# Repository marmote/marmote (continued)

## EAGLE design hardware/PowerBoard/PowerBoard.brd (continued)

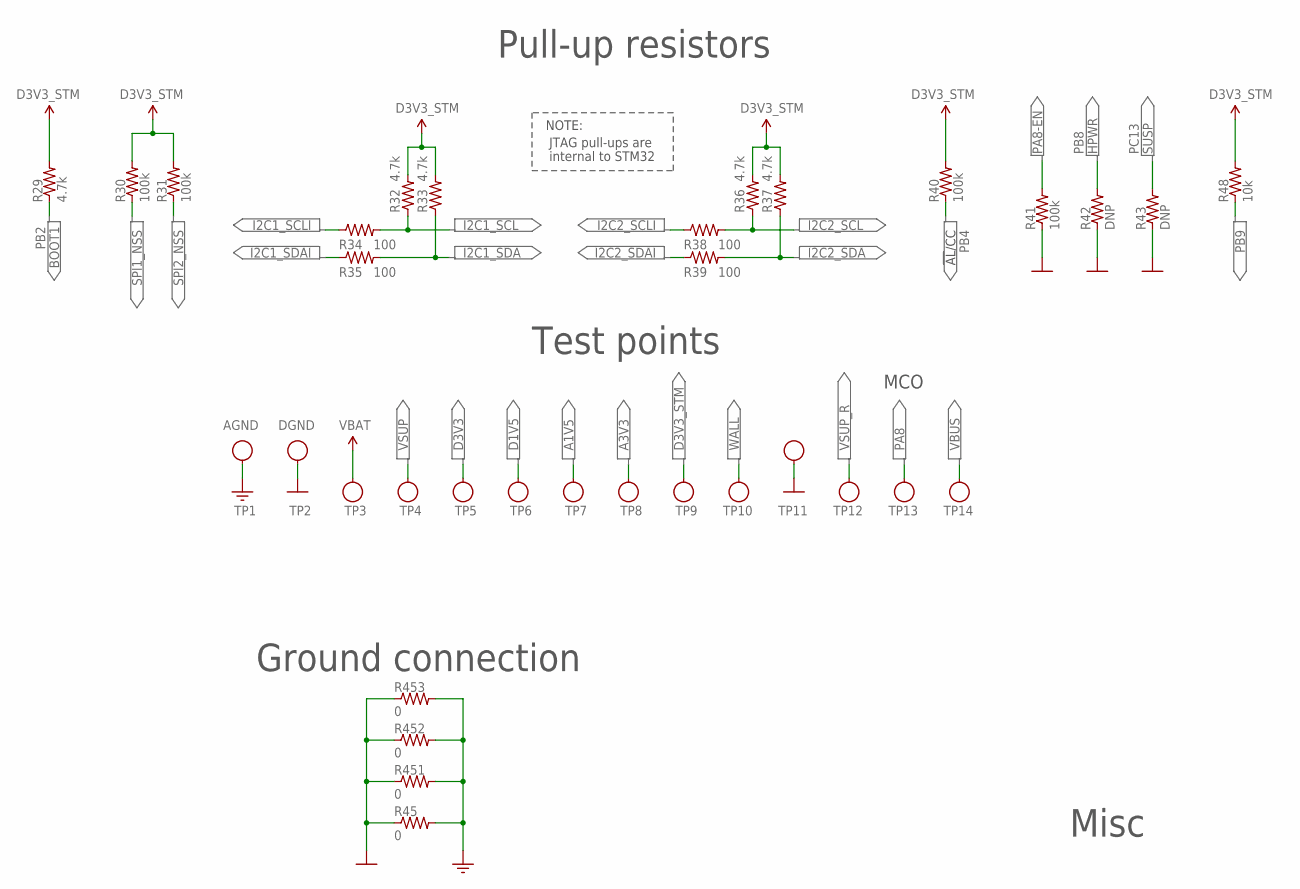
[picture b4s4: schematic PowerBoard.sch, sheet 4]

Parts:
R29, R32, R33, R36, R37: 4.7k; R0603
R30, R31, R40, R41: 100k; R0603
R34, R35, R38, R39: 100; R0603
R42, R43: DNP; R0603
R45, R451, R452, R453: 0; R0603
R48: 10k; R0603
TP1, TP2, TP3, TP4, TP5, TP6, TP7, TP8, TP9, TP10, TP11, TP12, TP13: TESTPOINT
TP14: TESTPOINT; MPN 5122; DIGI-KEY# 5122K-ND

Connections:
A1V5: TP7.1; also elsewhere on the board
A3V3: TP8.1; also elsewhere on the board
AGND: R45.2, R451.2, R452.2, R453.2, TP1.1; also elsewhere on the board
D1V5: TP6.1; also elsewhere on the board
D3V3: TP5.1; also elsewhere on the board
D3V3_STM: R29.2, R30.2, R31.2, R32.2, R33.2, R36.2, R37.2, R40.2, R48.2, TP9.1; also elsewhere on the board
DGND: R41.1, R42.1, R43.1, R45.1, R451.1, R452.1, R453.1, TP2.1, TP11.1; also elsewhere on the board
I2C1_SCL: R32.1, R34.2; also elsewhere on the board
I2C1_SCLI: R34.1; also elsewhere on the board
I2C1_SDA: R33.1, R35.2; also elsewhere on the board
I2C1_SDAI: R35.1; also elsewhere on the board
I2C2_SCL: R36.1, R38.2; also elsewhere on the board
I2C2_SCLI: R38.1; also elsewhere on the board
I2C2_SDA: R37.1, R39.2; also elsewhere on the board
I2C2_SDAI: R39.1; also elsewhere on the board
PA8: TP13.1; also elsewhere on the board
PA8-EN: R41.2; also elsewhere on the board
PB2: R29.1; also elsewhere on the board
PB4: R40.1; also elsewhere on the board
PB8: R42.2; also elsewhere on the board
PB9: R48.1; also elsewhere on the board
PC13: R43.2; also elsewhere on the board
SPI1_NSS: R30.1; also elsewhere on the board
SPI2_NSS: R31.1; also elsewhere on the board
VBAT: TP3.1; also elsewhere on the board
VBUS: TP14.1; also elsewhere on the board
VSUP: TP4.1; also elsewhere on the board
VSUP_R: TP12.1; also elsewhere on the board
WALL: TP10.1; also elsewhere on the board

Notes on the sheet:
Test points
Pull-up resistors
!AL!/CC
BOOT1
MCO
JTAG pull-ups are
internal to STM32
NOTE:
SUSP
HPWR
Ground connection

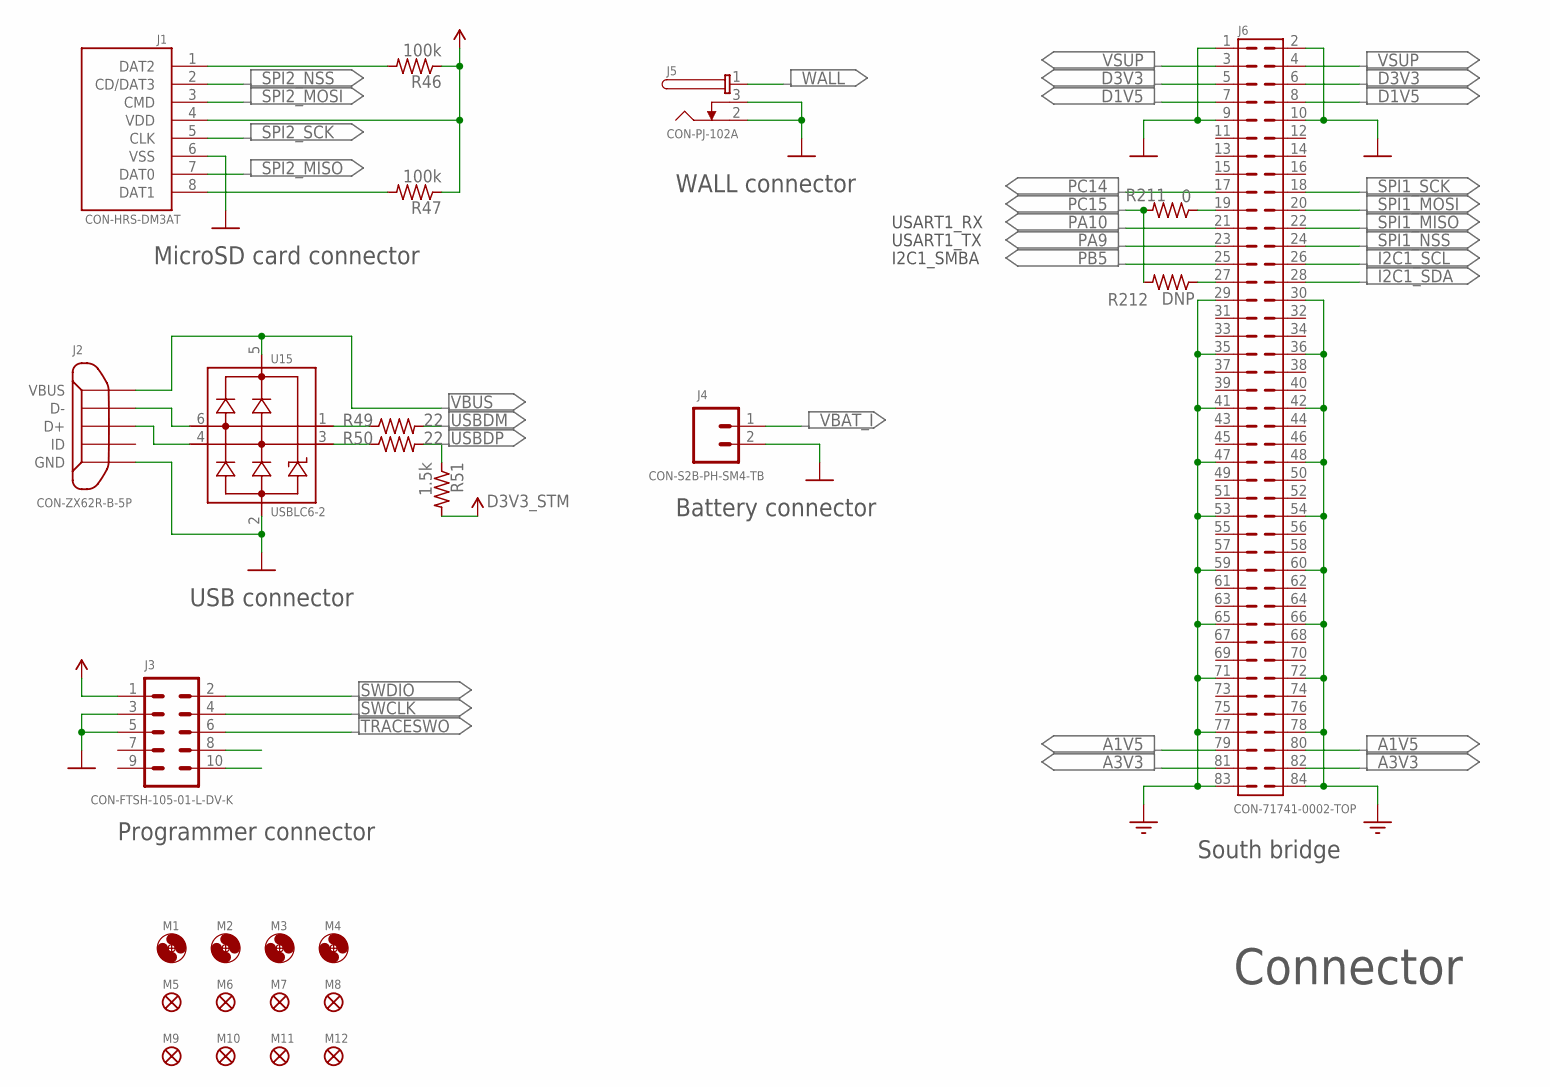
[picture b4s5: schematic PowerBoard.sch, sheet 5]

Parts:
J1: CON-HRS-DM3AT; HRS-DM3AT
J2: CON-ZX62R-B-5P; ZX62R-B-5P
J3: CON-FTSH-105-01-L-DV-K; FTSH-105-01-L-DV-K
J4: CON-S2B-PH-SM4-TB; S2B-PH-SM4-TB
J5: CON-PJ-102A; PJ-102A
J6: CON-71741-0002-TOP; 71741-0002
M1, M2, M3, M4: MOUNT-HOLE3.3; 3,3
M5, M6, M7, M8, M9, M10, M11, M12: FIDUCIAL1X2; FIDUCIAL-1X2
R46, R47: 100k; R0603
R49, R50: 22; R0603
R51: 1.5k; R0603
R211: 0; R0603
R212: DNP; R0603
U15: USBLC6-2; SOT23-6L

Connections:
A1V5: J6.79, J6.80; also elsewhere on the board
A3V3: J6.81, J6.82; also elsewhere on the board
AGND: J6.29, J6.30, J6.35, J6.36, J6.41, J6.42, J6.47, J6.48, J6.53, J6.54, J6.59, J6.60, J6.65, J6.66, J6.71, J6.72, J6.77, J6.78, J6.83, J6.84; also elsewhere on the board
D1V5: J6.7, J6.8; also elsewhere on the board
D3V3: J6.5, J6.6; also elsewhere on the board
D3V3_STM: J1.4 (VDD), J3.1, R46.1, R47.1, R51.2; also elsewhere on the board
DGND: J1.6 (VSS), J2.5 (GND), J3.3, J3.5, J4.2, J5.2, J5.3, J6.1, J6.2, J6.9, J6.10, U15.2 (GND); also elsewhere on the board
I2C1_SCL: J6.26; also elsewhere on the board
I2C1_SDA: J6.28; also elsewhere on the board
JNTRST: J3.10
JTDI: J3.8
unnamed: R50.1, U15.3 (IO2)
unnamed: R49.1, U15.1 (IO1)
unnamed: J6.27, R212.1
unnamed: J6.19, R211.1
unnamed: J1.1 (DAT2), R46.2
unnamed: J1.8 (DAT1), R47.2
PA9: J6.23; also elsewhere on the board
PA10: J6.21; also elsewhere on the board
PB5: J6.25; also elsewhere on the board
PC14: J6.17; also elsewhere on the board
PC15: R211.2, R212.2; also elsewhere on the board
SPI1_MISO: J6.22; also elsewhere on the board
SPI1_MOSI: J6.20; also elsewhere on the board
SPI1_NSS: J6.24; also elsewhere on the board
SPI1_SCK: J6.18; also elsewhere on the board
SPI2_MISO: J1.7 (DAT0); also elsewhere on the board
SPI2_MOSI: J1.3 (CMD); also elsewhere on the board
SPI2_NSS: J1.2 (CD/DAT3); also elsewhere on the board
SPI2_SCK: J1.5 (CLK); also elsewhere on the board
SWCLK: J3.4; also elsewhere on the board
SWDIO: J3.2; also elsewhere on the board
TRACESWO: J3.6; also elsewhere on the board
USBD+: J2.3 (D+), U15.4 (IO2)
USBD-: J2.2 (D-), U15.6 (IO1)
USBDM: R49.2; also elsewhere on the board
USBDP: R50.2, R51.1; also elsewhere on the board
VBAT_I: J4.1; also elsewhere on the board
VBUS: J2.1 (VBUS), U15.5 (VBUS); also elsewhere on the board
VSUP: J6.3, J6.4; also elsewhere on the board
WALL: J5.1; also elsewhere on the board

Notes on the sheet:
MicroSD card connector
South bridge
Programmer connector
USB connector
WALL connector
Battery connector
USART1_TX
USART1_RX
I2C1_SMBA

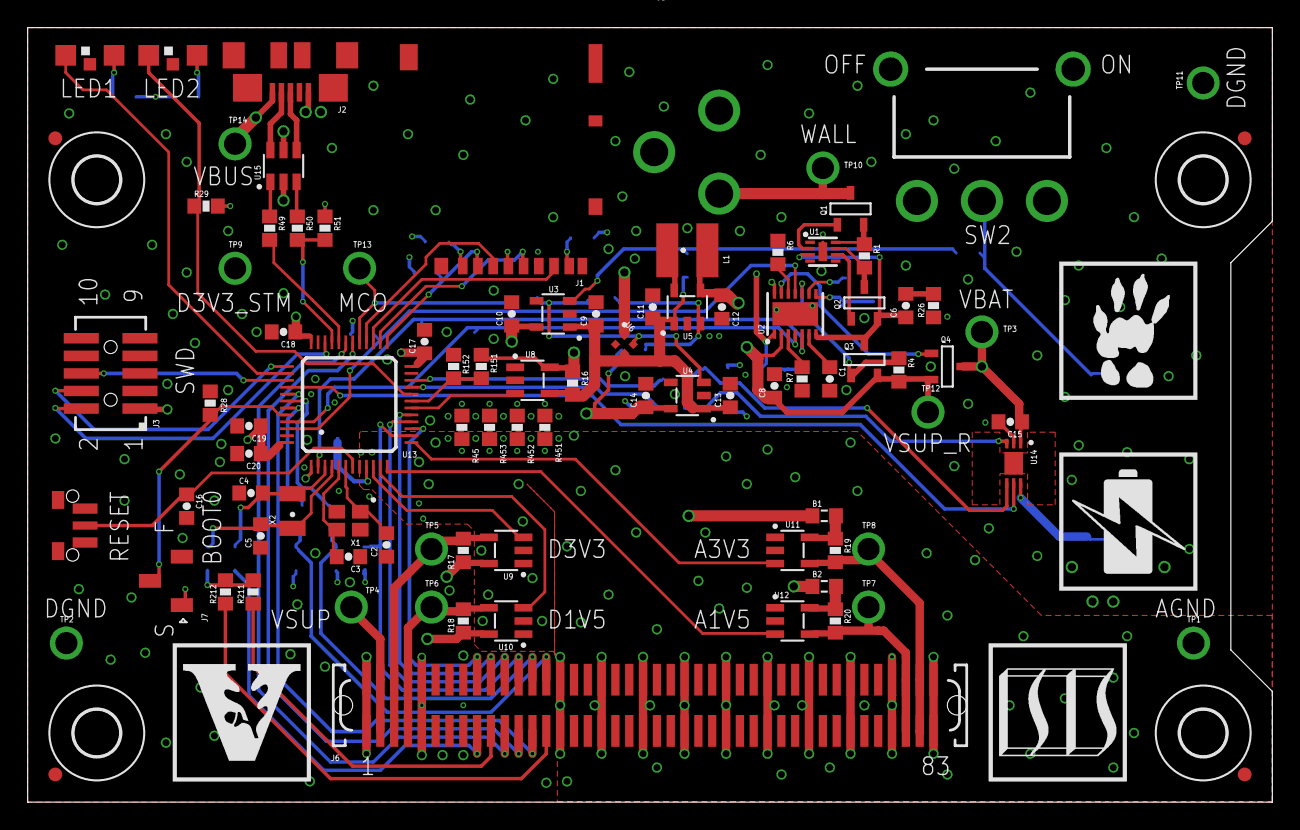
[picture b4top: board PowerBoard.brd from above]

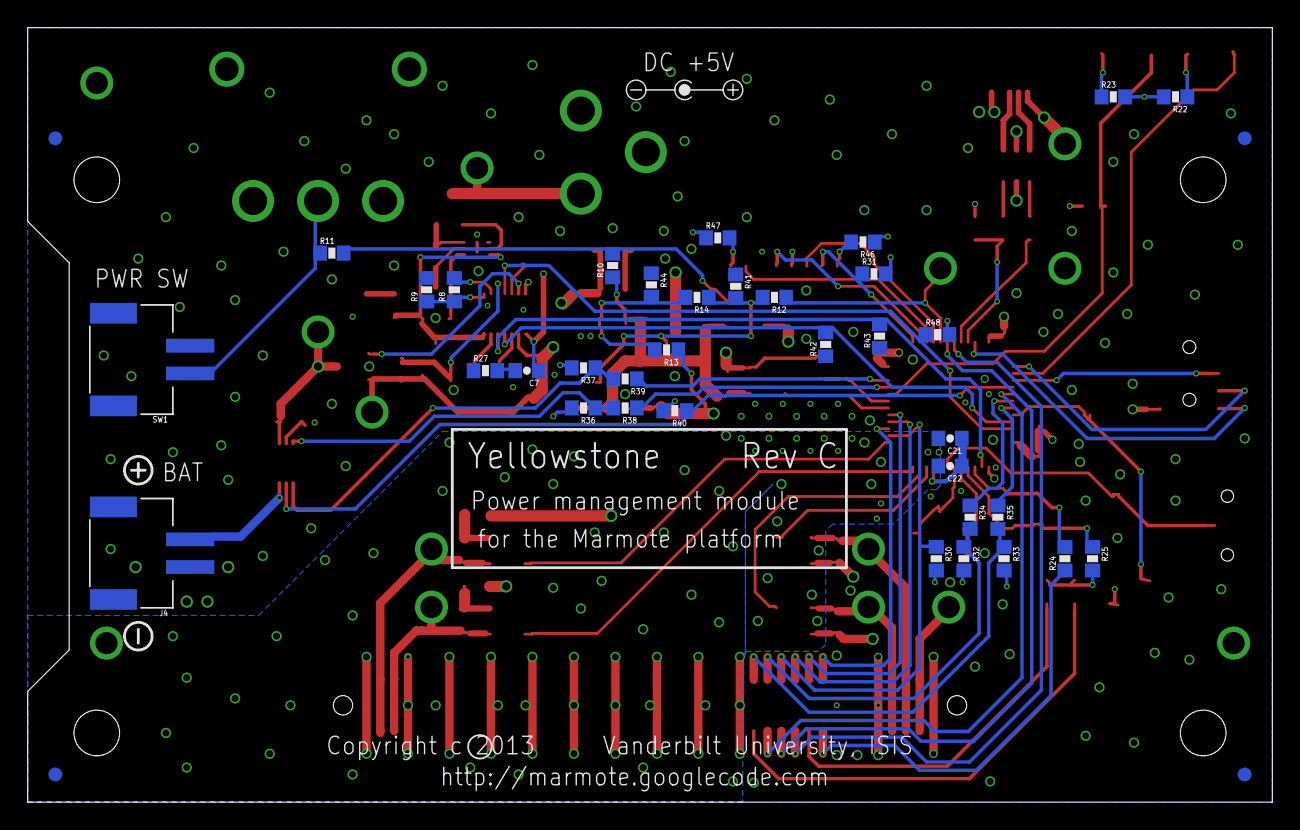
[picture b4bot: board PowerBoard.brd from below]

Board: 4 copper layers, 90.0 x 56.0 mm, 140 parts (39 on the bottom side), 92 nets.

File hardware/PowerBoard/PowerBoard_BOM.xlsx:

Bill of Materials for 'Marmote - Power Supply Board (Rev B)'
Item # | Reference | Value | Package | Manufacturer | Manufacturer Part # | Supplier | Supplier Part # | Details | Qty | Unit Price | Total Cost
1 | B1, B2 | 20mOhm@DC, 70Ohm@100MHz | BEAD0603 | Murata | BLM18SG700TN1D | Digi-Key | 490-5224-1-ND | FERRITE CHIP 70OHM 4A 0603 | 2 | 0.35299999999999998 | 0.70599999999999996
2 | C4, C5 | DNP | C0603 | TDK | C1608C0G1H040B | Digi-Key | 445-5028-1-ND | CAP CER 4.0PF 50V C0G 0603 | 2 | 0.16 | 0.32
3 | C2, C3 | 10pF | C0603 | TDK | C1608C0G1H100J | Digi-Key | 445-6852-1-ND | CAP CER 10PF 50V C0G 5% 0603 | 2 | 0.12 | 0.24
4 | C22 | 10nF | C0603 | TDK | C1608X7R1E103K | Digi-Key | 445-5100-1-ND | CAP CER 10000PF 25V X7R 10% 0603 | 1 | 0.08 | 0.08
5 | C15, C16, C17, C18, C19 | 0.1uF | C0603 | TDK | C1608X7R1C104K | Digi-Key | 445-1317-1-ND | CAP CER .10UF 16V 10% X7R 0603 | 5 | 0.08 | 0.4
6 | C1 | 0.15uF | C0603 | TDK | C1608X7R1C154K | Digi-Key | 445-5123-1-ND | CAP CER .15UF 16V 10% X7R 0603 | 1 | 0.2 | 0.2
7 | C21 | 1uF | C0603 | TDK | C1608X7R1C105K | Digi-Key | 445-1604-1-ND | CAP CER 1.0UF 16V X7R 10% 0603 | 1 | 0.23 | 0.23
8 | C7, C8, C10, C11, C14, C20 | 4.7uF | C0603 | TDK | C1608X5R0J475K | Digi-Key | 445-5178-1-ND | CAP CER 4.7UF 6.3V X5R 0603 | 6 | 0.36 | 2.16
9 | C6, C9, C12, C13 | 10uF | C0603 | TDK | C1608X5R0J106M | Digi-Key | 445-4112-1-ND | CAP CER 10UF 6.3V X5R 20% 0603 | 4 | 0.46 | 1.84
10 | J1 | CON-HRS-DM3AT | CON-HRS-DM3AT | Hirose | DM3AT-SF-PEJM5 | Digi-Key | HR1964CT-ND | CONN MICRO SD R/A PUSH-PUSH SMD | 1 | 3.01 | 3.01
11 | J2 | CON-ZX62R-B-5P | CON-ZX62R-B-5P | Hirose | ZX62R-B-5P | Digi-Key | H11574CT-ND | CONN RCPT MICRO USB B SMD R/A | 1 | 1.56 | 1.56
12 | J3 | CON-FTSH-105-01-L-DV-K | CON-FTSH-105-01-L-DV-K | Samtec | FTSH-105-01-L-DV-K | Digi-Key | FTSH-105-01-L-DV-K-ND | CONN HEADER 10 POS DUAL .05" SMD | 1 | 3.36 | 3.36
13 | J4, SW1 | CON-S2B-PH-SM4-TB | CON-S2B-PH-SM4-TB | JST | S2B-PH-SM4-TB(LF)(SN) | Digi-Key | 455-1749-1-ND | CONN HEADER PH SIDE 2POS 2MM SMD | 2 | 0.5 | 1
14 | J5 | CON-PJ-102A | CON-PJ-102A | CUI | PJ-102A | Digi-Key | CP-102A-ND | CONN JACK POWER 2.1MM PCB | 1 | 0.8 | 0.8
15 | J6 | CON-71741-0002 | CON-71741-0002 | Molex | 71741-0002 | Digi-Key | WM3498CT-ND | MEZZANINE 1MM BTB PLUG 84CKT | 1 | 6.24 | 6.24
16 | J7 | SWITCH-CJS-1200-1200 | J-Lead | CJS | CJS-1200TA | Digi-Key | 563-1021-1-ND | CJS-1200 SPDT Switch | 1 | 0.97 | 0.97
17 | L1 | 1.6uH | L-VLCF4018T | TDK | VLCF4018T-1R6N1R7-2 | Digi-Key | 445-3171-1-ND | INDUCTOR POWER 1.6UH 1.7A SMD | 1 | 0.72 | 0.72
18 | LED2 | ORANGE | LED1208-RA | Kingbright | APECVA3010SECK | Digi-Key | 754-1367-1-ND | LED 3X1MM 601NM ORN RA CHIP SMD | 1 | 0.28000000000000003 | 0.28000000000000003
19 | LED1 | GREEN | LED1208-RA | Kingbright | APECVA3010MGC | Digi-Key | 754-1364-1-ND | LED 3.0X1.0MM 568NM GRN RA SMD | 1 | 0.63 | 0.63
20 | Q1 | SI2323CDS | SI2323CDS | Vishay | SI2323CDS-T1-GE3 | Digi-Key | SI2323CDS-T1-GE3CT-ND | MOSFET P-CH 20V SOT-23 | 1 | 0.76 | 0.76
21 | Q2 | SI2312CDS | SI2312CDS | Vishay | SI2312CDS-T1-GE3 | Digi-Key | SI2312CDS-T1-GE3CT-ND | MOSFET N-CH 20V SOT-23 | 1 | 0.45 | 0.45
22 | Q3, Q4 | SI2333CDS | SI2333CDS | Vishay | SI2333CDS-T1-GE3 | Digi-Key | SI2333CDS-T1-GE3CT-ND | MOSFET P-CH D-S 12V SOT-23 | 2 | 0.84 | 1.68
23 | R13, R42, R43, R44, R212 | DNP | R0603 |  |  |  |  |  | 5 |  | 0
24 | R1, R12, R14, R211, R24, R25, R45, R451, R452, R453 | 0 | R0603 | Rohm | MCR03ERTJ000 | Digi-Key | RHM0.0GCT-ND | RES 0.0 OHM 1/10W 0603 SMD | 10 | 1.7999999999999999E-2 | 0.18
25 | R16, R17, R18, R19, R20 | 50m | R0603 | Vishay | WSL0603R0500FEA18 | Digi-Key | WSLL-.05CT-ND | RES .05 OHM 0.2W 1% 0603 SMD | 5 | 1.32 | 6.6000000000000005
26 | R26, R27 | 1 | R0603 | Rohm | MCR03EZPJ1R0 | Digi-Key | RHM1.0GCT-ND | RES 1.0 OHM 1/10W 5% 0603 SMD | 2 | 1.7999999999999999E-2 | 3.5999999999999997E-2
27 | R49, R50 | 22 | R0603 | Rohm | MCR03EZPFX22R0 | Digi-Key | RHM22.0HCT-ND | RES 22.0 OHM 1/10W 1% 0603 SMD | 2 | 2.3E-2 | 4.5999999999999999E-2
28 | R22, R34, R35, R38, R39 | 100 | R0603 | Rohm | MCR03ERTJ101 | Digi-Key | RHM100GCT-ND | RES 100 OHM 1/10W 5% 0603 SMD | 5 | 1.7999999999999999E-2 | 0.09
29 | R23 | 330 | R0603 | Rohm | MCR03EZPFX3300 | Digi-Key | RHM330HCT-ND | RES 330 OHM 1/10W 1% 0603 SMD | 1 | 2.3E-2 | 2.3E-2
30 | R51 | 1.5k | R0603 | Rohm | MCR03ERTF1501 | Digi-Key | RHM1.50KCFCT-ND | RES 1.50K OHM 1/10W 1% 0603 SMD | 1 | 0.21 | 0.21
31 | R7 | 2.1k | R0603 | Rohm | MCR03EZPFX2101 | Digi-Key | RHM2.10KHCT-ND | RES 2.10K OHM 1/10W 1% 0603 SMD | 1 | 2.3E-2 | 2.3E-2
32 | R11, R29, R32, R33, R36, R37 | 4.7k | R0603 | Rohm | MCR03ERTJ472 | Digi-Key | RHM4.7KGCT-ND | RES 4.7K OHM 1/10W 5% 0603 SMD | 6 | 1.7999999999999999E-2 | 0.10799999999999998
33 | R9 | 10k | NTCG06 | Vishay/Dale | NTHS0603N02N1002JE | Digi-Key | 541-1107-1-ND | THERMISTOR NTC 10K OHM 5% 0603 | 1 | 1 | 1
34 | R4, R8, R48 | 10k | R0603 | Rohm | MCR03ERTF1002 | Digi-Key | RHM10.0KHCT-ND | RES 10.0K OHM 1/10W 1% 0603 SMD | 3 | 2.3E-2 | 6.9000000000000006E-2
35 | R6, R10, R28, R30, R31, R40, R41, R46, R47, R151, R152 | 100k | R0603 | Rohm | MCR03ERTF1003 | Digi-Key | RHM100KHCT-ND | RES 100K OHM 1/10W 1% 0603 SMD | 11 | 2.3E-2 | 0.253
36 | SW2 | SWITCH-MS12ASG30 | SWITCH-MS12ASG30 | NKK | MS12ASG30 | Digi-Key | 360-2390-ND | SW SLIDE SPDT 0.4VA GOLD R/A PC | 1 | 5.45 | 5.45
37 | SW3 | SWITCH-ESWITCH-TL3340G | SWITCH-ESWITCH-TL3340G | E-Switch | TL3340AF160QG | Digi-Key | EG4627CT-ND | SWITCH TACTILE SPST-NO 0.05A 12V | 1 | 0.29099999999999998 | 0.29099999999999998
38 | TP3, TP4, TP5, TP6, TP9, TP10, TP12, TP14 | TESTPOINT | TESTPOINT-BLUE | Keystone | 5122 | Digi-Key | 5122K-ND | TEST POINT PC COMPACT T/H BLUE | 7 | 0.38 | 2.66
39 | TP7, TP8 | TESTPOINT | TESTPOINT-GREEN | Keystone | 5121 | Digi-Key | 5121K-ND | TEST POINT PC COMPACT T/H GREEN | 2 | 0.38 | 0.76
40 | TP13 | TESTPOINT | TESTPOINT-RED | Keystone | 5005 | Digi-Key | 5005K-ND | TEST POINT PC COMPACT .063"D RED | 1 | 0.36 | 0.36
41 | TP1, TP2, TP11 | TESTPOINT | TESTPOINT-YELLOW | Keystone | 5009 | Digi-Key | 5009K-ND | TEST POINT PC COMPACT .063"D YLW | 3 | 0.36 | 1.08
42 | U1 | LTC4361-2DC | LTC4361-2DC | Linear Technology | LTC4361IDC-2#TRMPBF | Digi-Key | LTC4361IDC-2#TRMPBFCT-ND | IC OVERVOLTAGE PROT CONT 8-DFN | 1 | 3.78 | 3.78
43 | U13 | STM32F10XCXT6 | STM32F10XCXT6 | STMicroelectronics | STM32F102CBT6 | Digi-Key | 497-8308-ND | MCU ARM 32BIT 128KB FLASH 48LQFP | 1 | 8.9499999999999993 | 8.9499999999999993
44 | U14 | LTC2942-1 | LTC2942-1 | Linear Technology | LTC2942CDCB-1#TRMPBF | Digi-Key | LTC2942CDCB-1#TRMPBFCT-ND | IC FUEL/GAS GAUGE LI-ION 1A 6DFN | 1 | 4.51 | 4.51
45 | U15 | USBLC6-2 | USBLC6-2 | STMicroelectronics | USBLC6-2SC6 | Digi-Key | 497-5235-1-ND | IC ESD PROTECTION LO CAP SOT23-6 | 1 | 1 | 1
46 | U2 | LTC4085 | LTC4085 | Linear Technology | LTC4085EDE#PBF | Digi-Key | LTC4085EDE#PBF-ND | IC USB POWER MANAGER 14-DFN | 1 | 3.3 | 3.3
47 | U3, U4 | XC6220B331MR-G | XC6220B331MR-G | Torex | XC6220B331MR-G | Digi-Key | 893-1133-1-ND | IC REG LDO 3.3V 1A SOT-25 | 2 | 0.88 | 1.76
48 | U5 | XC9236A15DMR-G | XC9236A15DMR-G | Torex | XC9236A15DMR-G | Digi-Key | 893-1120-1-ND | IC BUCK SYNC 1.5V .6A SOT-25 3MHZ | 1 | 1.5 | 1.5
49 | U6 | MIC94043 | MIC94043 | Micrel | MIC94043YFL TR | Digi-Key | 576-3228-1-ND | IC LOAD SW HISIDE 3A 4-MLF | 1 | 1.3 | 1.3
50 | U8, U9, U10, U11, U12 | MAX9938FEUK | MAX9938FEUK | Maxim | MAX9938FEUK+T | Digi-Key | MAX9938FEUK+TCT-ND | IC AMP CURRENT SENSE SOT23-5 | 5 | 1.68 | 8.4
51 | X1 |  | 4-SMD, No Lead (DFN, LCC) | TXC CORPORATION | 8Z-16.000MEEQ-T | Digi-Key | 887-1336-1-ND | CRYSTAL 16.000 MHZ 10PF SMD | 1 |  | 0
52 | X2 | DNP | ECX-31B | ECS | ECS-.327-7-34B-TR | Digi-Key | XC1656CT-ND | CRYSTAL 32.768 KHZ 7PF SMD | 1 | 1.26 | 1.26
53 | Standoff | DNP | MOUNT-HOLE3.3 | Keystone | 7200 | Digi-Key | 7200K-ND | STANDOFF HEX M/F .375"L 4-40 BR | 4 | 0.51500000000000001 | 2.06
 |  |  |  |  |  |  |  | Total | 127 |  | 84.695000000000022

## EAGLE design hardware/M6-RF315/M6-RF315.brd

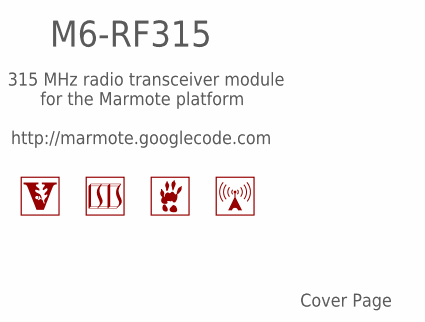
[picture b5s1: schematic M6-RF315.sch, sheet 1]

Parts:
LOGO1: LOGO-ISIS-600MIL-10MM-CU; LOGO-ISIS-10MM-COPPER
LOGO2: LOGO-MARMOTE-600MIL-10MM-CU; LOGO-MARMOTE-10MM-COPPER
LOGO3: LOGO-VANDERBILT-600MIL-10MM-CU; LOGO-VANDERBILT-10MM-COPPER
LOGO4: LOGO-RADIO-3-600MIL-10MM-CU; LOGO-RADIO-FILLED-10MM-COPPER

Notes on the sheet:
315 MHz radio transceiver module
http://marmote.googlecode.com
for the Marmote platform

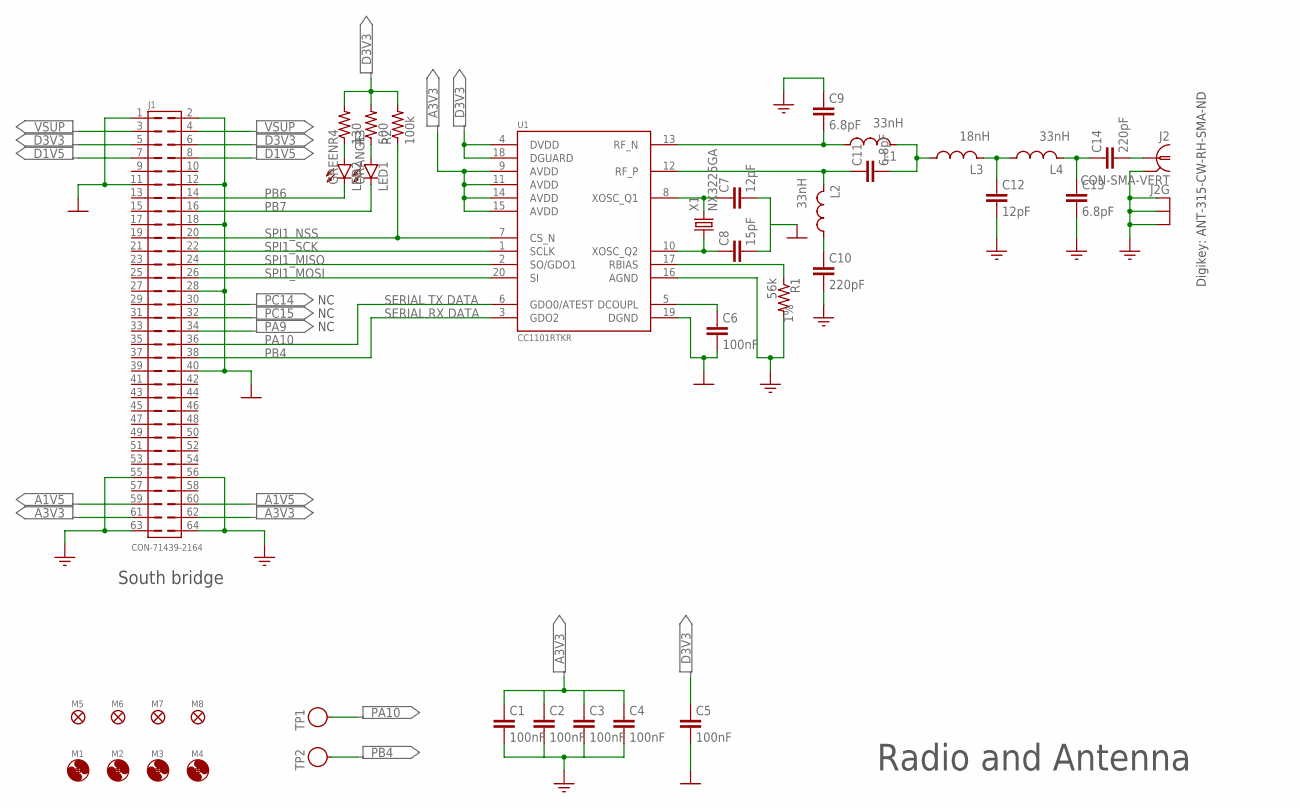
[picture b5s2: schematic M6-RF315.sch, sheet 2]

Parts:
C1, C2, C3, C4, C5, C6: 100nF; C0603
C7, C12: 12pF; C0603
C8: 15pF; C0603
C9, C11, C13: 6.8pF; C0603
C10, C14: 220pF; C0603
J1: CON-71439-2164; 71439-XX64-BOT
J2: CON-SMA-VERT; SMA-VERT; MPN 5-1814832-1
L1, L2, L4: 33nH; L0402
L3: 18nH; L0402
LED1: LED0603; MPN APT1608SECK; DIGI-KEY# 754-1120-1-ND
LED2: LED0603; MPN APT1608MGC; DIGI-KEY# 754-1118-1-ND
M1, M2, M3, M4: MOUNT-HOLE3.3; 3,3
M5, M6, M7, M8: FIDUCIAL1X2; FIDUCIAL-1X2
R1: 56k; R0603; TOLERANCE 1%
R2: 100k; R0603
R3: 500; R0603
R4: 130; R0603
TP1, TP2: TESTPOINT-RED; TESTPOINT
U1: CC1101RTKR; QFN-20
X1: NX3225GA

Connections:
A1V5: J1.59, J1.60
A3V3: C1.1, C2.1, C3.1, C4.1, J1.61, J1.62, U1.9 (AVDD), U1.11 (AVDD), U1.14 (AVDD), U1.15 (AVDD)
AGND: C1.2, C2.2, C3.2, C4.2, C9.1, C10.2, C12.2, C13.2, J1.55, J1.56, J1.63, J1.64, J2.2 (GND), J2.3 (GND), J2.4 (GND), J2.5 (GND), R1.2, U1.16 (AGND), U1.EXP (AGND)
D1V5: J1.7, J1.8
D3V3: C5.1, J1.5, J1.6, R2.2, R3.2, R4.2, U1.4 (DVDD), U1.18 (DGUARD)
DGND: C5.2, C6.2, C7.2, C8.2, J1.1, J1.2, J1.11, J1.12, J1.18, J1.28, J1.40, U1.19 (DGND), X1.2 (DGND), X1.4 (DGND)
unnamed: LED1.A, R3.1
unnamed: C12.1, L3.2, L4.1
unnamed: C6.1, U1.5 (DCOUPL)
unnamed: C8.1, U1.10 (XOSC_Q2), X1.1
unnamed: C7.1, U1.8 (XOSC_Q1), X1.3 (2)
unnamed: C11.1, L2.2, U1.12 (RF_P)
unnamed: C9.2, L1.1, U1.13 (RF_N)
unnamed: C11.2, L1.2, L3.1
unnamed: C13.1, C14.1, L4.2
unnamed: C14.2, J2.1
unnamed: C10.1, L2.1
unnamed: LED2.A, R4.1
PA9: J1.34
PA10: J1.36, TP1.1, U1.6 (GDO0/ATEST)
PB4: J1.38, TP2.1, U1.3 (GDO2)
PB6: J1.14, LED2.C
PB7: J1.16, LED1.C
PC14: J1.30
PC15: J1.32
RBIAS: R1.1, U1.17 (RBIAS)
SPI1_MISO: J1.24, U1.2 (SO/GDO1)
SPI1_MOSI: J1.26, U1.20 (SI)
SPI1_NSS: J1.20, R2.1, U1.7 (CS_N)
SPI1_SCK: J1.22, U1.1 (SCLK)
VSUP: J1.3, J1.4

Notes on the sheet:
South bridge
SERIAL TX DATA
SERIAL RX DATA
Digikey: ANT-315-CW-RH-SMA-ND

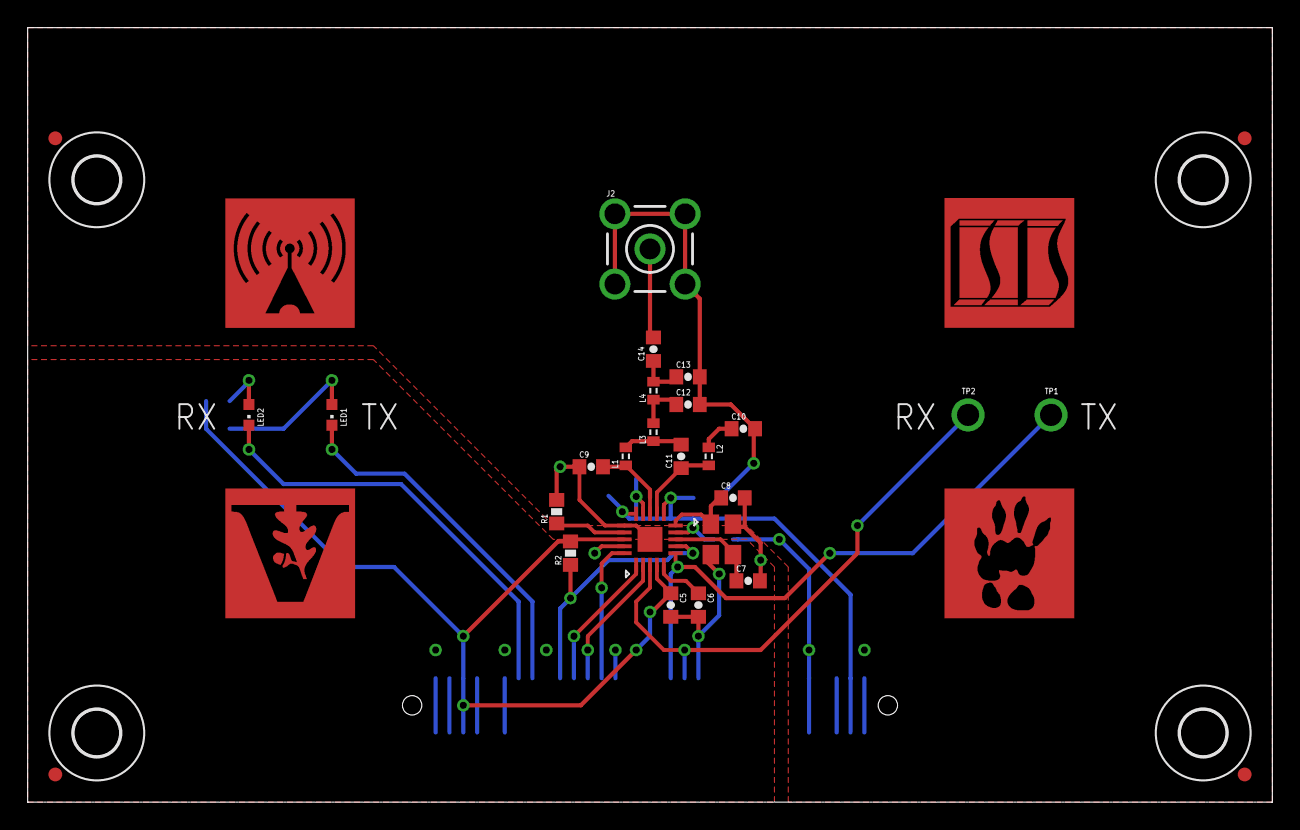
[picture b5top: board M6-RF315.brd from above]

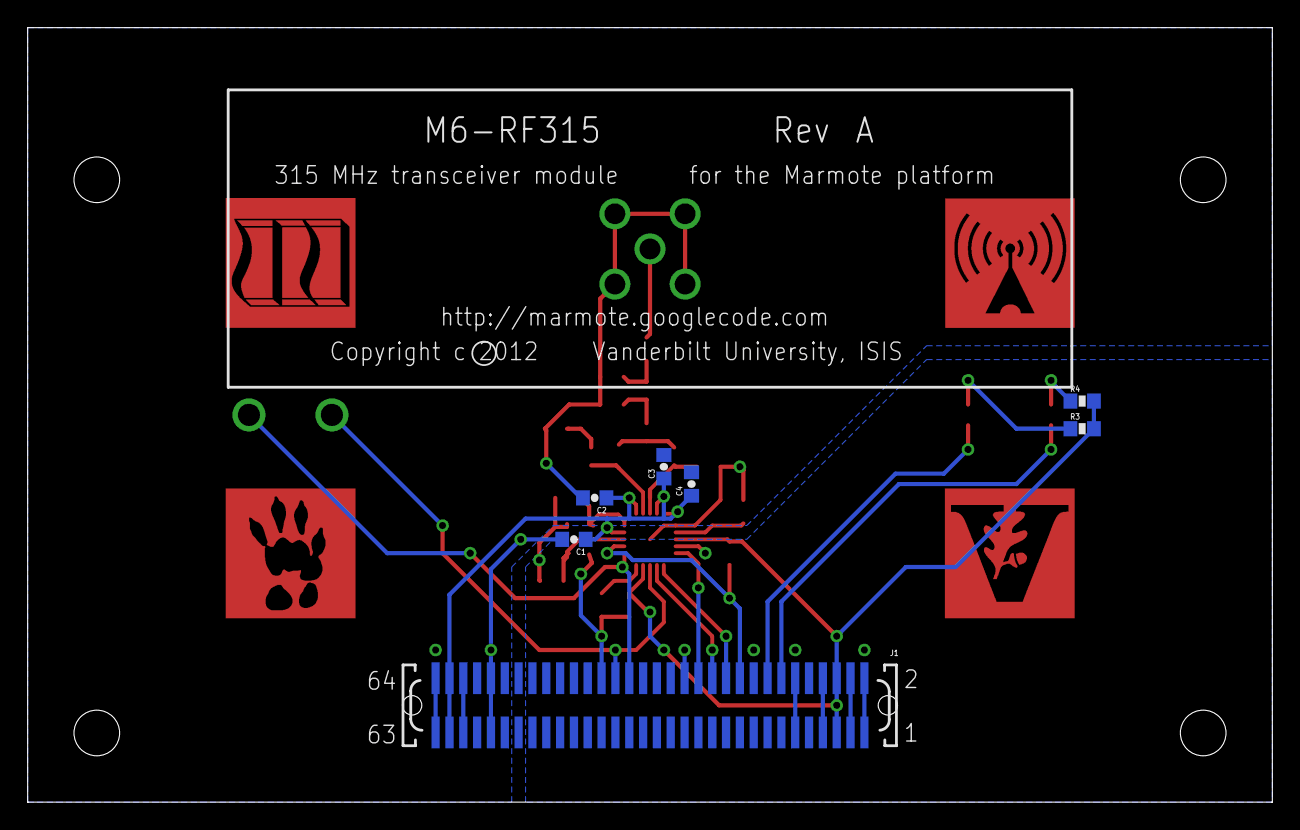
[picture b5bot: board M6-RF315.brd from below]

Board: 2 copper layers, 90.0 x 56.0 mm, 42 parts (7 on the bottom side), 28 nets.

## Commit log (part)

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2013-03-05 The FskTransmitter design modified for TX path calibration. (Intermediate check-in.)
2013-03-06 Finished the simulation of the I/Q compensation block.
2013-03-07 CORDIC based transmitter path debugging/testing design.
2013-03-07 Replaced the CORDIC sine generator with a 4x1024 element SINE TABLE and a 64-bit phase accumulator. (C code needs to be adjusted.)
2013-03-11 Minor cleanup regarding HLS code generation.
2013-03-11 Moved the GMSK_SYNC block to the canvas.
2013-03-11 Created a branch to implement the CDMA (DSSS) transmitter path.
2013-03-11 Adjusted the sync_pattern for GMSK_SYNC.
2013-03-11 Intermediate check-in. Do not use this version.
2013-03-30 - Minor changes in plotting
2013-04-03 - Reciprocal onset time picker with minimum as onset time - License added to notebooks
2013-04-04 - Title added
2013-04-23 Updated the design for Teton Rev B and Yellowstone Rev B.
2013-04-24 - RF board BOMs updated with switches
2013-04-25 Created directory for the GNU Radio applications and tools.
2013-04-25 Added basic GNU Radio blocks to test USRP/Marmote GMSK communication.
2013-04-25 Added GNU Radio GMSK transmitter message lenght handling.
2013-04-27 Added a GMSK loopback companion design
2013-04-27 Added a GMSK message sink block (currently implements frame synchronizer only).
2013-04-28 Added GMSK packet sink frame and payload handling.
2013-04-29 Added GNU Radio GMSK frame handler to the receiver side.
2013-04-29 Tested the GMSK receiver with a Marmote transmitter.
2013-04-30 Updated design for Rev B pinout.
2013-04-30 Minor adjustments to packet handling and block parameters.
2013-05-01 Steel beam analysis added
2013-05-02 - Distance calculation bug corrected
2013-05-06 Added traffic_generator to avoid glitches after packet transmission.
2013-05-15 - Sound speed calculation updated
2013-05-18 Started to work with PN sequences.
2013-05-18 Added a maximum sequence DS spreader block.
2013-05-21 Added CDMA packet source and sink blocks.
2013-05-21 Started implementing the PN spreader block.
2013-05-22 Added maximum-sequence shift register for PN code generation.
2013-05-22 Added a primitive PN synchronizer.
2013-05-22 Created a skeleton Tx/Rx processing path for the CDMA design.
2013-05-23 Intermediate check-in.
2013-05-23 Testing the despreader block.
2013-05-23 Tested the loopback chain with a single transmitter and single receiver.
2013-05-24 Still debugging pn_despreader.
2013-05-27 Minor adjustments, switched to REF_CLK.
2013-06-04 Started to add oversampling receiver.
2013-06-04 Added support for oversampling on the receiver side.
2013-06-04 Smaller project clean-up.
2013-06-04 Added python asynchronous message_source block.
2013-06-05 Minor fixes in message_source.py.
2013-06-06 Modified the transmit chain and added a differential encoder.
2013-06-07 Improved pn_synchronizer detection scheme. (Still using threshold logic.)
2013-06-11 Reverted to fixed-threshold-based synchronizer and added support for differential decoding.
2013-06-12 Added a simple pn_generator block.
2013-06-12 Generalized the PN-sequence generator to support shift registers with up to 32-bit widths.
2013-06-17 Added a PN sequence generator to the transmit path.
2013-06-18 Added a differential encoder to the transmit path and applied minor fixes to the PN sequence generator.
2013-06-18 Intermediate check-in before designing a raised-cosine filter.
2013-06-18 Added a 31-tap RRC pulse shaping filter to the transmit path (takes 27% of the fabric logic).
2013-06-20 7-byte-payload design used for single-transmitter DSSS measurements (node).
2013-06-20 7-byte-payload design used for single-transmitter DSSS measurements (host).
2013-06-20 Check-in before testing the GMSK-BPSK transceiver.
2013-06-21 Modified design to fixed packet length.
2013-06-23 Intermediate check-in (needs clean-up).
2013-06-24 Added avg_min to the PN synchronizer block interface.
2013-06-24 Intermediate check-in, do not use this version.
2013-06-25 Added payload CRC16 check to D-BPSK CDMA RX.
2013-06-25 Added Matlab script to test PN-sequences and updated the firmware accordingly.
2013-06-25 Made 'packet length', 'spread factor' and 'preamble length' adjustable from the console.
2013-06-25 Parametrized setup for measurements (node).
2013-06-25 Parametrized setup for measurements (host).
2013-06-26 The design used for D-BPSK CDMA measurements.
2013-06-26 Design to be used for D-BPSK CDMA measurements.
2013-06-26 Revision used for first CDMA measurements.
2013-06-27 Added a command to control the variance of the packet transmission intervals.
2013-06-27 Move SPI command processing to teton.h.
2013-07-03 Fixed d_peak_idx bug resulting in synchronization tag glitches.
2013-07-03 Fixed a differential-decoding related bug. (Revision contains debug code and needs clean up.)
2013-07-10 Created directory for the TinyOS-based CSMA transmitter tests.
2013-07-10 Initial check-in with TimerMilliC.
2013-08-01 Added a binary XOR-based PN-matched filter for synchronization.
2013-08-01 Added oversampling support to the binary PN-matched filter.
2013-08-01 Added bpsk_cdma_tx path GRC block (not tested yet).
2013-08-02 Updated project to GNU Radio 3.7.0 format.
2013-08-05 Added initial version of peak_tagger.
2013-08-06 Added QA code to peak_tagger.
2013-08-06 Added integer output binary slicer block.
2013-08-06 Started to add QA code for the PN acquisition block.
2013-08-28 Updated cdma_packet_sink statistic generation
2013-08-28 Added total_packet to cdma_packet_sink interface
2013-08-28 Added grc file for despreading comparison
2013-08-28 Checked in rx companion design for 'online' testing
2013-09-05 Parameterized the message transmission interval
2013-09-10 Switched from PER to PPR and fixed a SEQ overflow issue
2013-09-10 Revision used for DSSS PER-distance measurements
2013-09-11 Added measurement evaluation scripts and stripped packet_sink output
2013-09-12 Created Ofdm directory.
2013-09-12 Use CdmaTransceiver project as a base for Ofdm.
2013-09-12 Started to clean up Ofdm project directory.
2013-09-13 Added guards and search for peak minima.
2013-09-13 Started to set up the unit test simulation.
2013-09-13 Instantiated the IFFT_16 module in the transmit path and created the corresponding unit test.
2013-09-16 Recreated the design from scratch because a core update (CoreAPB) and/or a SP install messed up the project files. (Firmware still needs a cleanup.)
2013-09-16 Cleaned-up the timing constraint file.
2013-09-16 Updated CoreAPB3 bus addressing scheme and added APB BFM test.
2013-09-16 Cleaned up firmware and added EFROM configuration file.
2013-09-17 Updated Simulink model fixed-point representation and IFFT input scaling.
2013-09-17 Added pretty-print and hex-input for ptrn (pattern) and mask commands.
2013-09-17 Added digital output gain control logic/firmware code.
2013-09-17 Added N_FFT/2 offset to subcarrier indexing.
2013-09-17 Modified CmdTxBw to use 'MHz' range instead of 'kHz'.
2013-09-17 Added command to periodically rotate subcarrier phases by 180 degrees.
2013-09-20 Revision used for preliminary indoor phase measurements.
2013-09-23 Added STAPL programming file to the revision used for preliminary (16-subcarrier OFDM) indoor phase measurements.
2013-09-23 Tag for the 16-subcarrier OFDM-based continuous transmitter design.
2013-09-23 Updated design to 32-point OFDM.
2013-09-23 Modified the 'periodic mode' to toggle between on and off.
2013-09-23 Committed the corresponding STAPL file.
2013-09-24 Added a 256x32 TX_FIFO and a draft for a high-level TX_FSM.
2013-09-24 Intermediate check-in before restructuring the design. (Do not use this version.)
2013-09-24 Added IFFT_CTRL block. Intermediate check-in while restructuring the design. (Do not use this version.)
2013-09-25 Added an OFDM-based 'MarmotE' waterfall demo option.
2013-09-25 Added Simulink model for cyclic-prefixer.
2013-09-26 Intermediate check-in of the Simulink OFDM transmitter model.
2013-09-26 Added timing logic for to hold off after the last transmitted symbol (to empty the IFFT pipeline).
2013-09-26 Corrected a bug causing a glitch in the first transmitted symbol.
2013-09-26 Added gain control logic to the OFDM TX Simulink model.
2013-09-27 Reorganized and cleaned up the Simulink model.
2013-09-27 STAPL file for the OFDM-based MarmotE-banner demo.
2013-09-27 Replaced IFFT_CTRL and IFFT (generated) blocks with Simulink generated OFDM transmitter path. (Needs further fixing.)
2013-09-28 Fixed the CP timing. (Simulink model needs cleanup.)
2013-09-28 Added a custom FIFO to the CP block in Simulink.
2013-09-30 Started to integrate the Simulink OFDM transmitter design into the Libero project.
2013-09-30 Updated firmware to accommodate the new FPGA design.
2013-10-01 Added initial version of the measurement script
2013-10-01 Fixed some bugs in mm_rx_cfile.sh
2013-10-03 Set up battery alarm and cleaned up several files.
2013-10-03 Added errata item on PWM timers
2013-10-03 Edited wiki page PowerBoardErrata through web user interface.
2013-10-03 Updated LED2 (orange) behavior: 0.5 Hz toggle -> charging; blinking at 1 Hz -> low battery
2013-10-04 - Improved wavelet analysis
2013-10-04 - Onset time selection in wavelet bands - initial tests
2013-10-06 - Onset time selection in bands - Modified time-frequency display
2013-10-16 Fixed battery gauge alarm initialization/handling.
2013-10-17 Minor cleanups and added new default (even and odd) MASK and PTRN parameters.
2013-10-17 Added 'tx [1 | 2]' command to simplify measurement initialization.
2013-10-17 Updated mm_rx_cfile recorder script for larger node count setups
2013-10-28 Added 'sweep' command to automate field measurements.
2013-10-28 Added preset masks. Intermediate check-in, needs a huge cleanup.
2013-10-29 Added bash script for USRP measurements (sweep).
2013-10-29 Modified the microcontroller code for 'sweep' type measurements.
2013-11-25 Created wiki page through web user interface.
2013-11-25 Edited wiki page Publications through web user interface.
2013-12-05 Clustering working
2013-12-12 Normal distribution on 2D histogram
2013-12-15 - Rearranging stuff - Minor changes
2013-12-16 - Restructuring - Notebooks should run now
2013-12-16 Onset time and Wavelet Ipython notebooks updated
2014-01-02 - 3D histogram added - Kolmogorov-Smirnov test - Metropolis Markov Chain Monte Carlo method testing for arbitrary random variable generation
2014-01-02 - Histogram updated - Metropolis Markov Chain Monte Carlo notebook descriptions added
2014-01-06 - Clustering functions moved separate files
2014-01-10 Clustering based on steepness
2014-01-10 - TODO added for Beaver Board rev B
2014-01-12 - Clustering bugs corrected - Anderson-Darling test - Best cluster selection
2014-01-12 Clustering bug corrected
2014-01-13 Clustering in all AE notebooks
2014-01-15 Wavelet analysis best basis selection cleaned up
2014-02-21 Seems to be a missing commit from right after the experiments...
2014-04-03 Added empirical CDF calculator Kolmogorov-Smirnov test updated
2014-04-04 Event arrival hypothesis tests
2014-04-07 Rearranged notebooks
2015-03-14 Migrating wiki contents from Google Code
